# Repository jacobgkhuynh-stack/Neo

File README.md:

# Neo
I followed the week 4 guide and made a controllable ring light for soldering SMD parts. It also has a rotary encoder on to for it we be easily controlled

|Item                    |Qty|Supplier                        |Cost/item|Total Cost|link                                                                                                                                                                                                                                                                                                                                                                                                                                                                                                                                                                                                                                                             |
|------------------------|---|--------------------------------|---------|----------|-----------------------------------------------------------------------------------------------------------------------------------------------------------------------------------------------------------------------------------------------------------------------------------------------------------------------------------------------------------------------------------------------------------------------------------------------------------------------------------------------------------------------------------------------------------------------------------------------------------------------------------------------------------------|
|USB-C 6pin receptacle   |1  |ZANHDZBF Official Store         |$4.90    |$4.90     |https://www.aliexpress.us/item/3256812173793524.html?spm=a2g0o.productlist.main.19.68913401qWfQJY&algo_pvid=733b4382-56ce-44f8-971d-319afd5229c3&algo_exp_id=733b4382-56ce-44f8-971d-319afd5229c3-18&pdp_ext_f=%7B%22order%22%3A%2234%22%2C%22eval%22%3A%221%22%2C%22fromPage%22%3A%22search%22%7D&pdp_npi=6%40dis%21USD%214.90%211.09%21%21%2132.44%217.24%21%402101ca9517935760805053151e0e6a%2112000058188632061%21sea%21US%210%21ABX%211%210%21n_tag%3A-29910%3Bd%3A92917014%3Bm03_new_user%3A-29895%3BpisId%3A5000000218165384&curPageLogUid=YAqG6a6WPMhf&utparam-url=scene%3Asearch%7Cquery_from%3A%7Cx_object_id%3A1005012360108276%7C_p_origin_prod%3A   |
|EC11                    |1  |StarLanguage Store              |$3.45    |$3.45     |https://www.aliexpress.us/item/2255800160725313.html?spm=a2g0o.productlist.main.3.159a1757sJfygl&algo_pvid=676d7605-0cb4-4361-9c8b-558c4bfbb5d5&algo_exp_id=676d7605-0cb4-4361-9c8b-558c4bfbb5d5-2&pdp_ext_f=%7B%22order%22%3A%22328%22%2C%22eval%22%3A%221%22%2C%22fromPage%22%3A%22search%22%7D&pdp_npi=6%40dis%21USD%213.45%211.09%21%21%213.45%211.09%21%402101ca8b17935922064612804e0e50%2110000001431232375%21sea%21US%210%21ABX%211%210%21n_tag%3A-29910%3Bd%3A92917014%3Bm03_new_user%3A-29895%3BpisId%3A5000000218165391&curPageLogUid=AyXETNIdN8PH&utparam-url=scene%3Asearch%7Cquery_from%3A%7Cx_object_id%3A4000347040065%7C_p_origin_prod%3A        |
|Xiao esp32 s3           |1  |Seeedstudio AI Hardware Store   |$10.92   |$10.92    |https://www.aliexpress.us/item/3256808047100037.html?spm=a2g0o.productlist.main.2.48402ec3jCcuvW&algo_pvid=b4d18204-5ecb-4e7b-a1f8-9c74f1714836&algo_exp_id=b4d18204-5ecb-4e7b-a1f8-9c74f1714836-1&pdp_ext_f=%7B%22order%22%3A%22850%22%2C%22eval%22%3A%221%22%2C%22fromPage%22%3A%22search%22%7D&pdp_npi=6%40dis%21USD%2130.35%2112.86%21%21%21200.85%2185.12%21%402101ca9517935922953077021e0e07%2112000058240791889%21sea%21US%210%21ABX%211%210%21n_tag%3A-29910%3Bd%3A92917014%3Bm03_new_user%3A-29895%3BpisId%3A5000000218165391&curPageLogUid=DLvTi7LMcN6a&utparam-url=scene%3Asearch%7Cquery_from%3A%7Cx_object_id%3A1005008233414789%7C_p_origin_prod%3A|
|SK6812 RGBW             |1  |XUNATA Light-Life Discount Store|$1.09    |$1.09     |https://www.aliexpress.us/item/3256801785673787.html?spm=a2g0o.productlist.main.9.1f4f628etTIfaH&algo_pvid=bbf1268d-a617-463f-b5b5-982f5c223fe9&algo_exp_id=bbf1268d-a617-463f-b5b5-982f5c223fe9-8&pdp_ext_f=%7B%22order%22%3A%22620%22%2C%22eval%22%3A%221%22%2C%22fromPage%22%3A%22search%22%7D&pdp_npi=6%40dis%21USD%2111.21%211.09%21%21%2111.21%211.09%21%4021032e4e17935924786686807e0d0b%2112000040418758421%21sea%21US%210%21ABX%211%210%21n_tag%3A-29910%3Bd%3A92917014%3Bm03_new_user%3A-29895%3BpisId%3A5000000218165391&curPageLogUid=Jag28jOKPd5O&utparam-url=scene%3Asearch%7Cquery_from%3A%7Cx_object_id%3A1005001971988539%7C_p_origin_prod%3A   |
|PCB                     |1  |JLCPCB                          |$1.50    |$1.50     |https://jlcpcb.com/                                                                                                                                                                                                                                                                                                                                                                                                                                                                                                                                                                                                                                              |
|Estimated total shipping|1  |                                |         |$2.62     |                                                                                                                                                                                                                                                                                                                                                                                                                                                                                                                                                                                                                                                                 |

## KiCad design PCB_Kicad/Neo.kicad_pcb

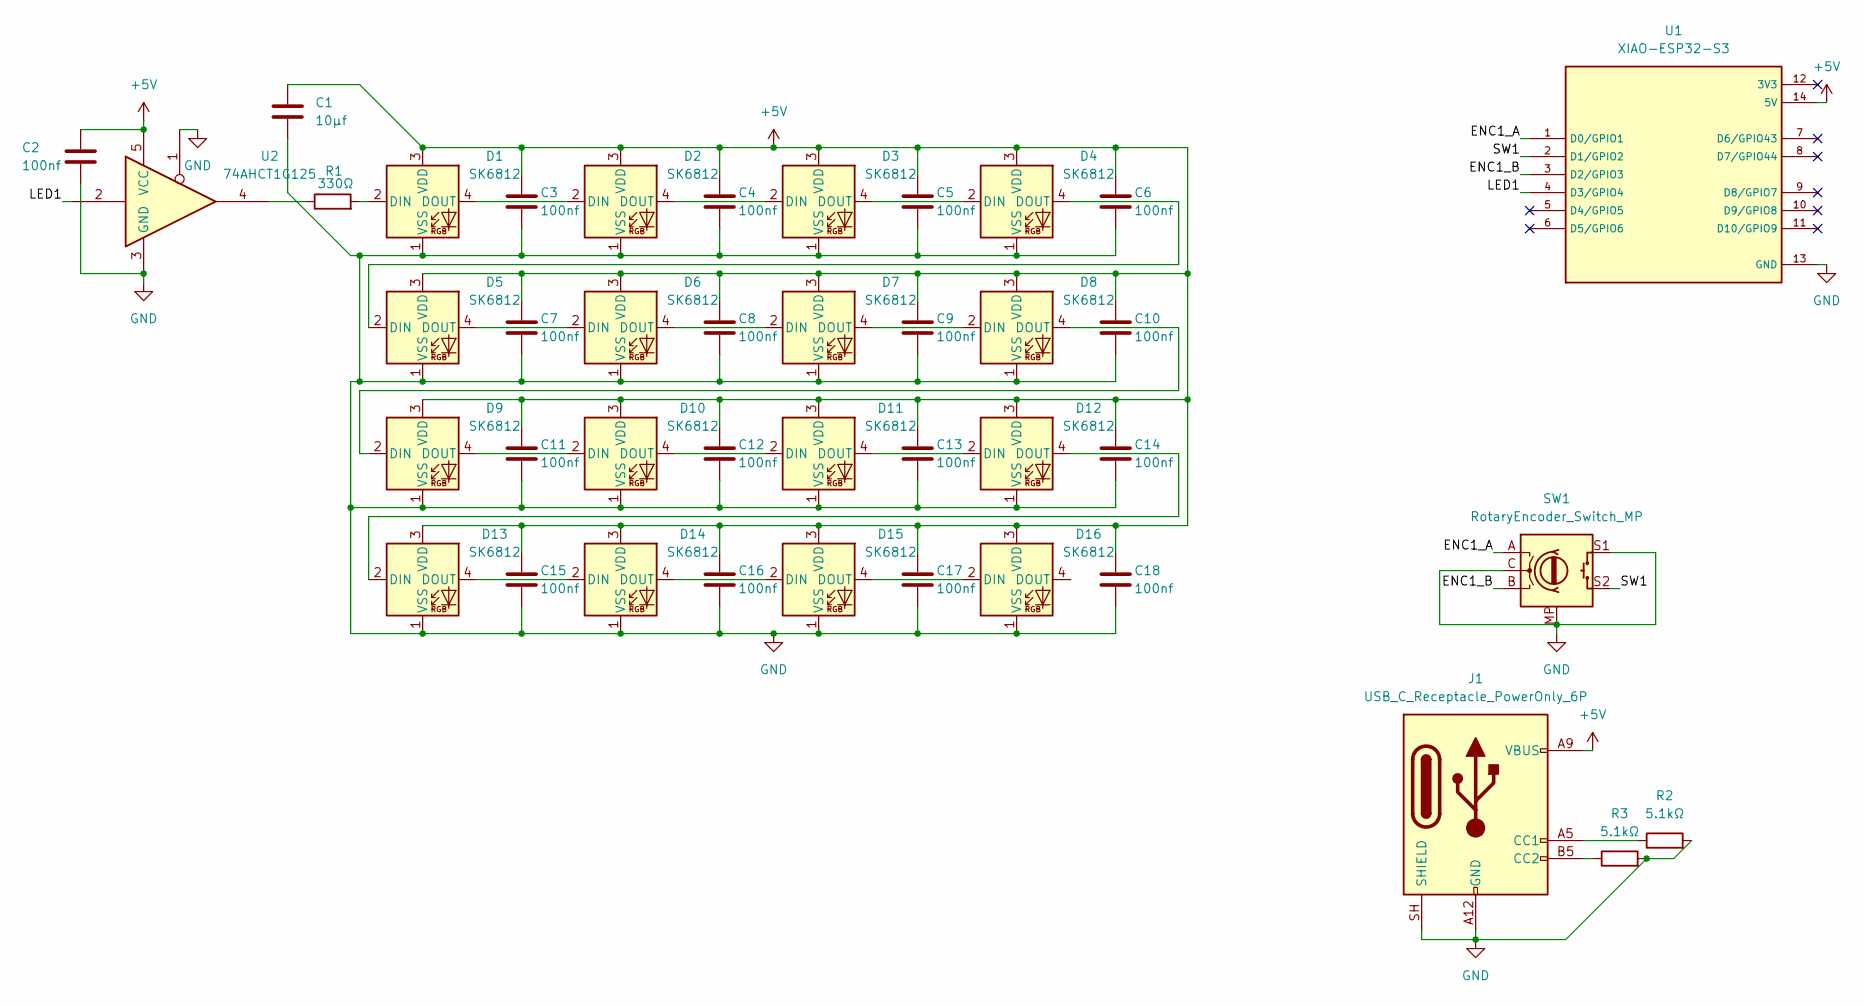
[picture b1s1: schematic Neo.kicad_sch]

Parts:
C1: 10µf; C_0603_1608Metric_Pad1.08x0.95mm_HandSolder
C2, C3, C4, C5, C6, C7, C8, C9, C10, C11, C12, C13, C14, C15, C16, C17, C18: 100nf; C_0603_1608Metric_Pad1.08x0.95mm_HandSolder
D1, D2, D3, D4, D5, D6, D7, D8, D9, D10, D11, D12, D13, D14, D15, D16: SK6812; LED_SK6812_PLCC4_5.0x5.0mm_P3.2mm
J1: USB_C_Receptacle_PowerOnly_6P; USB_C_Receptacle_GCT_USB4125-xx-x_6P_TopMnt_Horizontal
R1: 330Ω; R_0603_1608Metric_Pad0.98x0.95mm_HandSolder
R2, R3: 5.1kΩ; R_0603_1608Metric_Pad0.98x0.95mm_HandSolder
SW1: RotaryEncoder_Switch_MP; RotaryEncoder_Alps_EC11E-Switch_Vertical_H20mm
U1: XIAO-ESP32-S3; XIAO-ESP32-S3-SMD; PARTREV April 22nd, 2026
U2: 74AHCT1G125; SOT-23-5_HandSoldering

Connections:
+5V: C1.1, C2.1, C3.1, C4.1, C5.1, C6.1, C7.1, C8.1, C9.1, C10.1, C11.1, C12.1, C13.1, C14.1, C15.1, C16.1, C17.1, C18.1, D1.3 (VDD), D2.3 (VDD), D3.3 (VDD), D4.3 (VDD), D5.3 (VDD), D6.3 (VDD), D7.3 (VDD), D8.3 (VDD), D9.3 (VDD), D10.3 (VDD), D11.3 (VDD), D12.3 (VDD), D13.3 (VDD), D14.3 (VDD), D15.3 (VDD), D16.3 (VDD), J1.A9 (VBUS), J1.B9 (VBUS), U1.14 (5V), U2.5 (VCC)
/ENC1_A: SW1.A, U1.1 (D0/GPIO1)
/ENC1_B: SW1.B, U1.3 (D2/GPIO3)
/LED1: U1.4 (D3/GPIO4), U2.2
/SW1: SW1.S2, U1.2 (D1/GPIO2)
GND: C1.2, C2.2, C3.2, C4.2, C5.2, C6.2, C7.2, C8.2, C9.2, C10.2, C11.2, C12.2, C13.2, C14.2, C15.2, C16.2, C17.2, C18.2, D1.1 (VSS), D2.1 (VSS), D3.1 (VSS), D4.1 (VSS), D5.1 (VSS), D6.1 (VSS), D7.1 (VSS), D8.1 (VSS), D9.1 (VSS), D10.1 (VSS), D11.1 (VSS), D12.1 (VSS), D13.1 (VSS), D14.1 (VSS), D15.1 (VSS), D16.1 (VSS), J1.A12 (GND), J1.B12 (GND), J1.SH (SHIELD), R2.2, R3.2, SW1.C, SW1.MP, SW1.S1, U1.13 (GND), U2.1, U2.3 (GND)
unnamed: D1.2 (DIN), R1.2
unnamed: D1.4 (DOUT), D2.2 (DIN)
unnamed: D2.4 (DOUT), D3.2 (DIN)
unnamed: D3.4 (DOUT), D4.2 (DIN)
unnamed: D4.4 (DOUT), D5.2 (DIN)
unnamed: D5.4 (DOUT), D6.2 (DIN)
unnamed: D6.4 (DOUT), D7.2 (DIN)
unnamed: D7.4 (DOUT), D8.2 (DIN)
unnamed: D8.4 (DOUT), D9.2 (DIN)
unnamed: D9.4 (DOUT), D10.2 (DIN)
unnamed: D10.4 (DOUT), D11.2 (DIN)
unnamed: D11.4 (DOUT), D12.2 (DIN)
unnamed: D12.4 (DOUT), D13.2 (DIN)
unnamed: D13.4 (DOUT), D14.2 (DIN)
unnamed: D14.4 (DOUT), D15.2 (DIN)
unnamed: D15.4 (DOUT), D16.2 (DIN)
unnamed: J1.A5 (CC1), R2.1
unnamed: J1.B5 (CC2), R3.1
unnamed: R1.1, U2.4

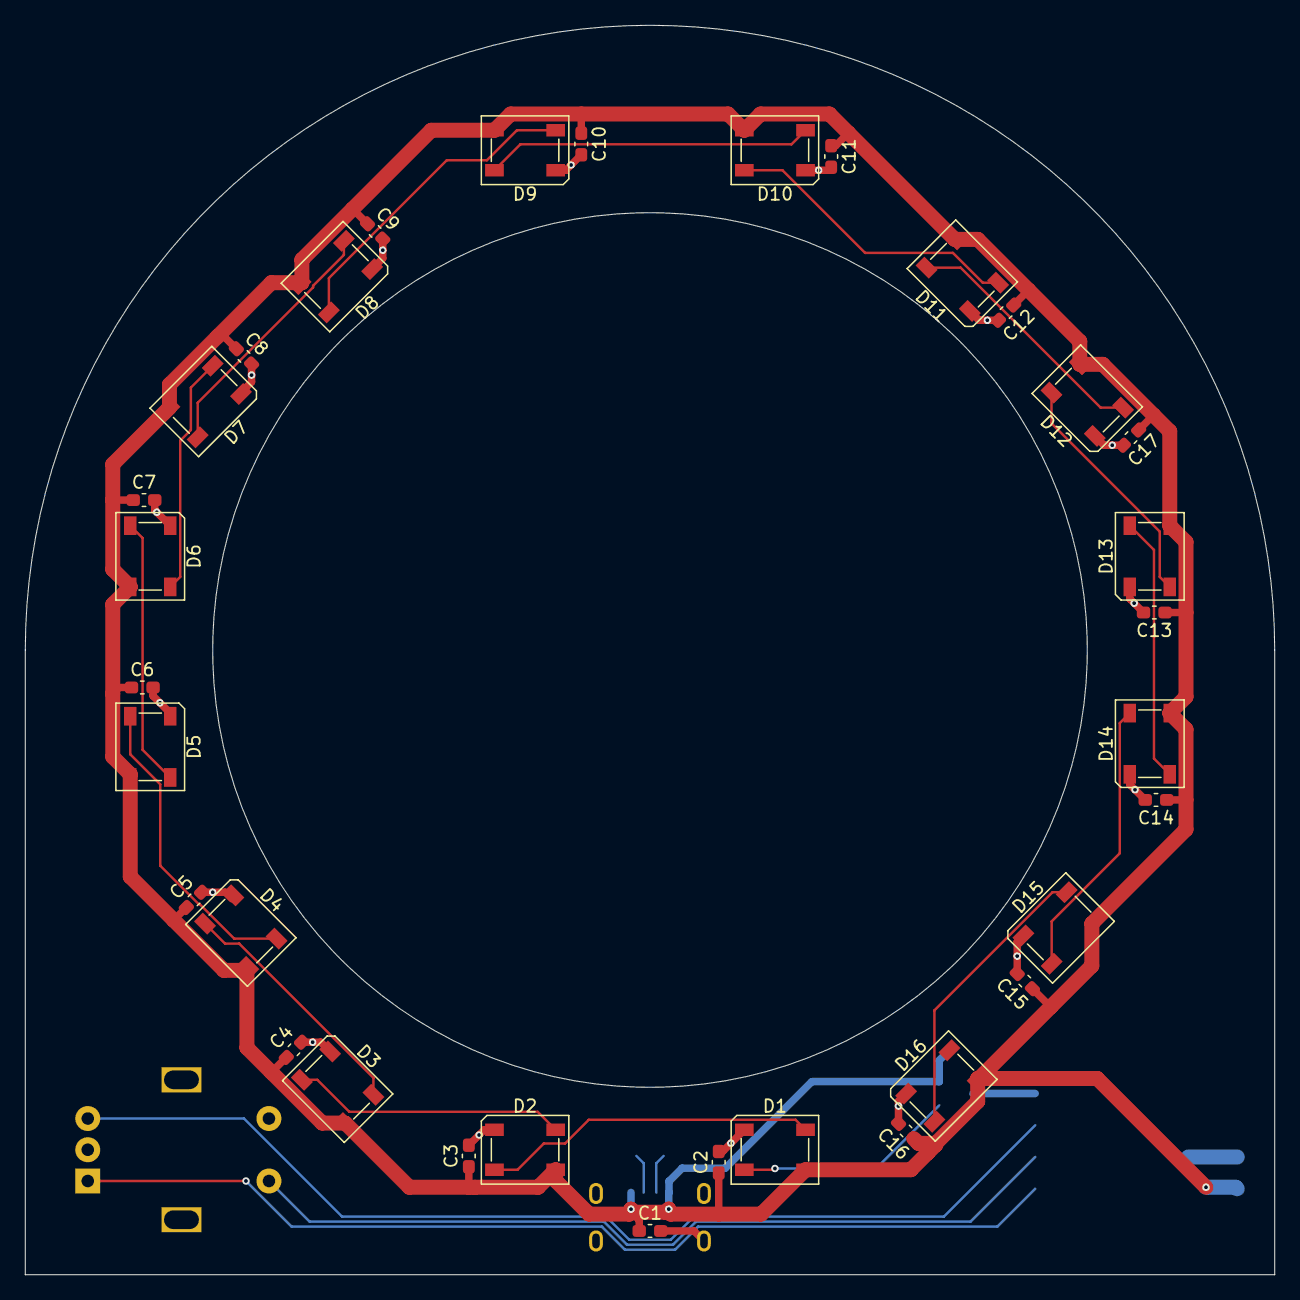
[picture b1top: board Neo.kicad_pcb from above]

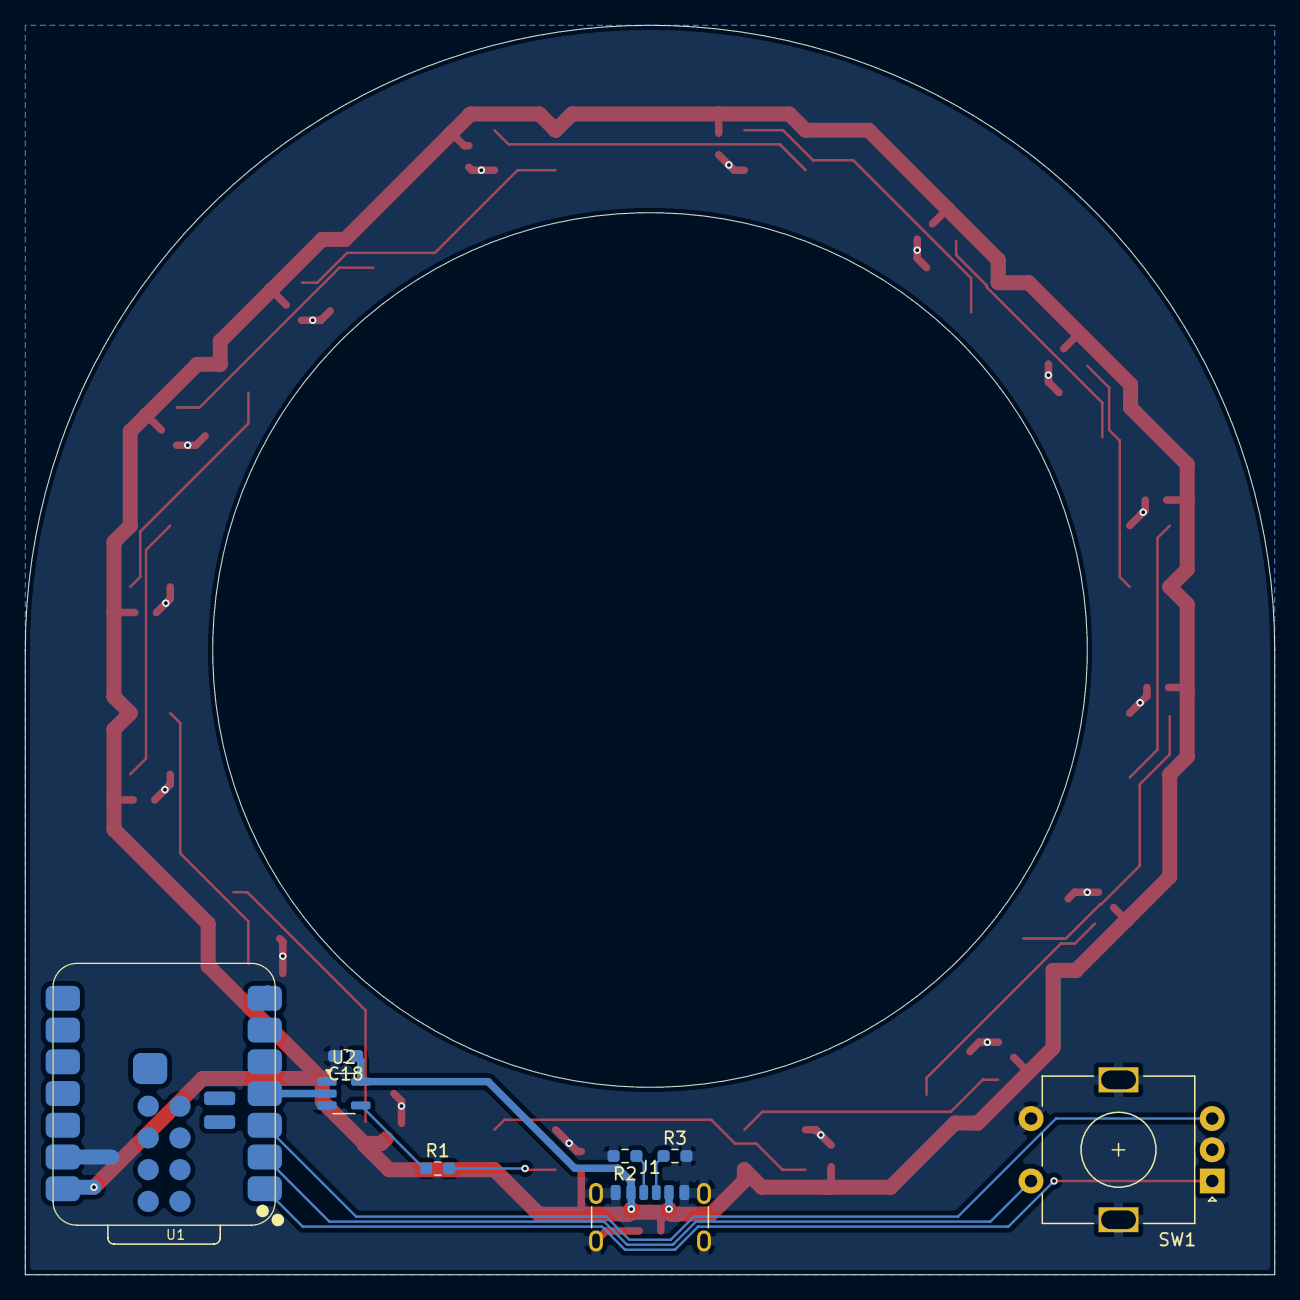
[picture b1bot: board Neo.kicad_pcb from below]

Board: 2 copper layers, 100.0 x 100.0 mm, 41 parts (8 on the bottom side), 25 nets.

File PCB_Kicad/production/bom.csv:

Designator,Footprint,Quantity,Value,LCSC Part #
C1,0603,1,10µf,
"C10, C11, C12, C13, C14, C15, C16, C17, C18, C2, C3, C4, C5, C6, C7, C8, C9",0603,17,100nf,
"D1, D10, D11, D12, D13, D14, D15, D16, D2, D3, D4, D5, D6, D7, D8, D9",LED_SK6812_PLCC4_5.0x5.0mm_P3.2mm,16,SK6812,
J1,USB_C_Receptacle_GCT_USB4125-xx-x_6P_TopMnt_Horizontal,1,USB_C_Receptacle_PowerOnly_6P,
R1,0603,1,330Ω,
"R2, R3",0603,2,5.1kΩ,
SW1,RotaryEncoder_Alps_EC11E-Switch_Vertical_H20mm,1,RotaryEncoder_Switch_MP,
U1,XIAO-ESP32-S3-SMD,1,XIAO-ESP32-S3,
U2,SOT-23-5_HandSoldering,1,74AHCT1G125,
